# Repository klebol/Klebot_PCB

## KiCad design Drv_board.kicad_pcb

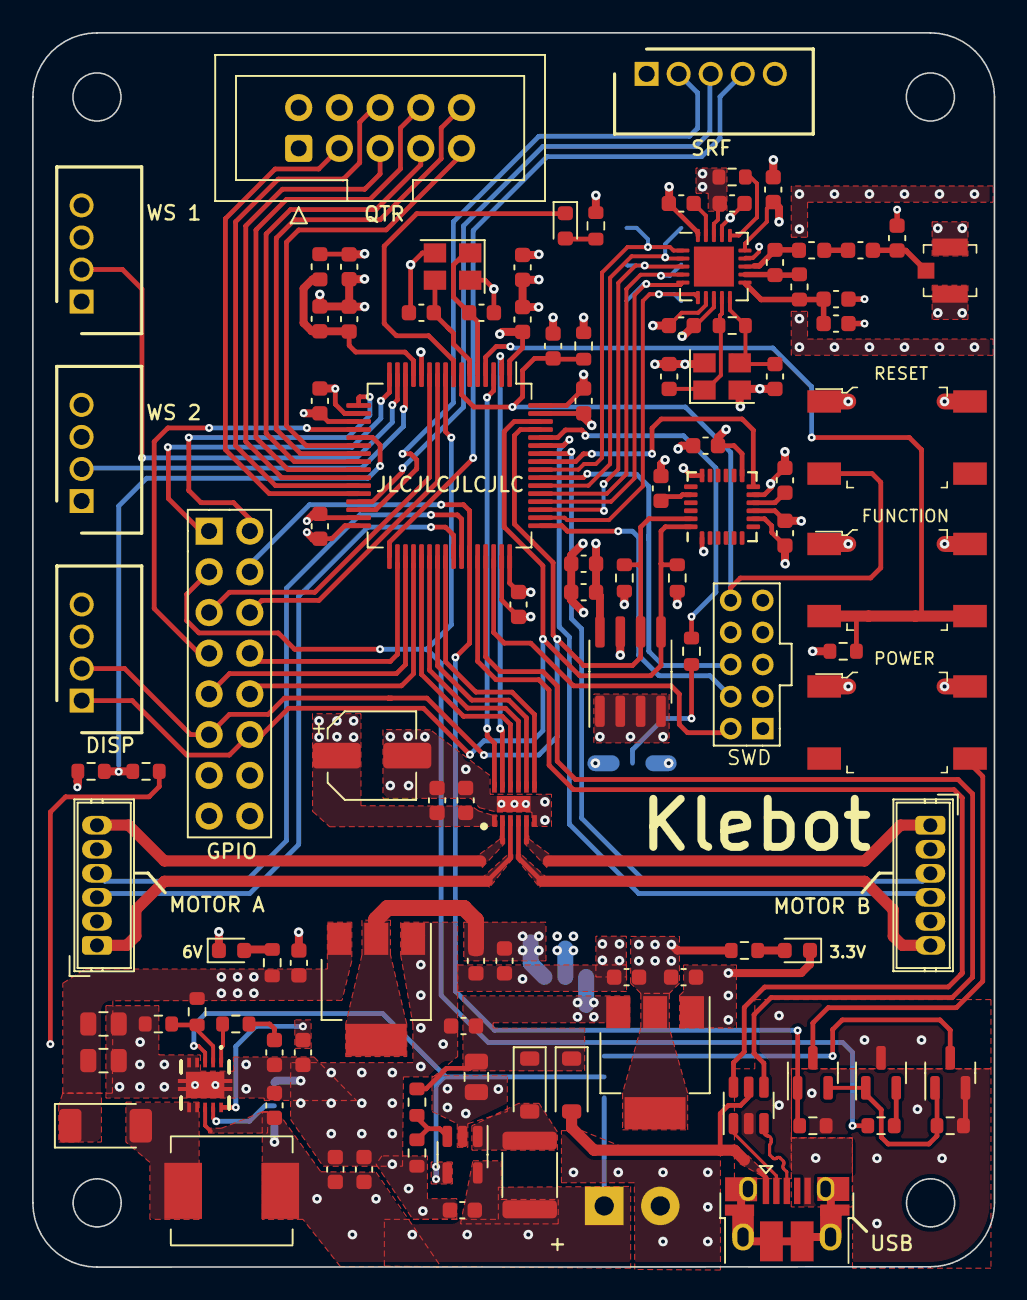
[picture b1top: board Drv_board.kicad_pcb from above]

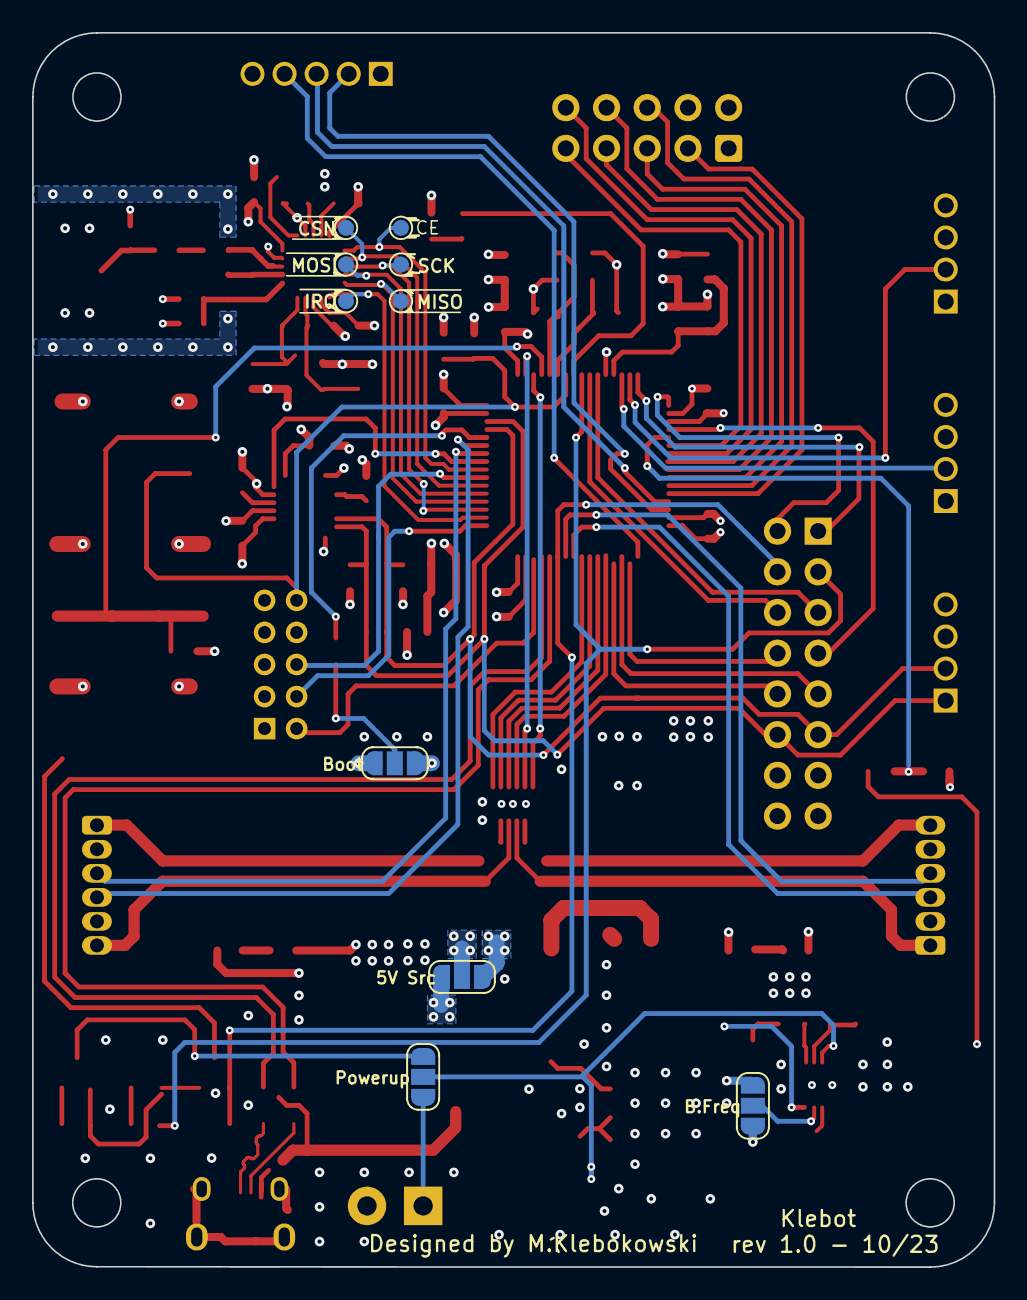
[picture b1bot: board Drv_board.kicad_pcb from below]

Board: 4 copper layers, 60.0 x 77.0 mm, 118 parts (10 on the bottom side), 96 nets.

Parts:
BT1: Battery; TerminalBlock_Phoenix_PT-1,5-2-3.5-H_1x02_P3.50mm_Horizontal
C1: 4u7; C_0603_1608Metric
C2, C3, C4, C5, C6, C10, C18, C20, C23, C25, C27, C30, C33, C34, C35, C42, C43, C45: 100n; C_0603_1608Metric
C7, C41: 10n; C_0603_1608Metric
C8, C9, C13: 1u; C_0603_1608Metric
C11, C12, C36, C37: 10p; C_0603_1608Metric
C14, C15, C19, C26, C29: 10u; C_0603_1608Metric
C16, C17: 22u; C_0805_2012Metric
C21: 4u7 6.3V; C_0603_1608Metric
C22: 22uF 6.3V; C_0805_2012Metric
C24: 2n7; C_0603_1608Metric
C28: 47u; CP_Elec_5x5.9
C31: 1p5; C_0603_1608Metric
C32: 1p; C_0603_1608Metric
C38, C46: 2n2; C_0603_1608Metric
C39: 4p7; C_0603_1608Metric
C40: 33n; C_0603_1608Metric
C44: 2u2; C_0603_1608Metric
D1: LED BLUE; LED_0603_1608Metric
D2: BAT54C; SOT-23
D3, D5: 40V 1A; D_SOD-123
D4: PMEG6030ETPX; D_SOD-128
D6: LED RED; LED_0603_1608Metric
D7: LED ORANGE; LED_0603_1608Metric
FB1: 120R; L_0603_1608Metric
IC1: TPS61087DRCR
IC2: DRV8836DSSR; SON50P200X300X80-13N-D
J1: USB_B_Micro; USB_Micro-B_Amphenol_10103594-0001LF_Horizontal
J2: WS_LED_1_CONN; SHDR4W55P0X200_1X4_1000X500X530P
J3: WS_LED_0_CONN; SHDR4W55P0X200_1X4_1000X500X530P
J4: QTR_CONN; IDC-Header_2x05_P2.54mm_Vertical
J5: SRF-05_CONN; SHDR5W55P0X200_1X5_1200X500X530P
J6: OLED_CONN; SHDR4W55P0X200_1X4_1000X500X530P
J7: SWD; PinHeader_2x05_P2.00mm_Vertical
J8: Motor A; Wuerth_WR-WTB_64800611622_1x06_P1.50mm_Vertical
J9: Motor B; Wuerth_WR-WTB_64800611622_1x06_P1.50mm_Vertical
J10: U.FL; Coax_Conn_U.FL
J11: BREAKOUT; PinHeader_2x08_P2.54mm_Vertical
JP1: 5V Source; SolderJumper-3_P1.3mm_Open_RoundedPad1.0x1.5mm
JP2: Powerup Mode; SolderJumper-3_P1.3mm_Open_RoundedPad1.0x1.5mm
JP3: Boost Converter Freqency; SolderJumper-3_P1.3mm_Open_RoundedPad1.0x1.5mm
L1: 4u7; L_Neosid_SM-PIC0602H
L2: 4.7uH 650mA; L_1812_4532Metric
L3: 3n9; L_0603_1608Metric
L4: 8n2; L_0603_1608Metric
L5: 2n7; L_0603_1608Metric
Q1: DMP2045U; SOT-23
Q2: BC847-QR; SOT-23
R1, R2, R4: 10k; R_0603_1608Metric
R3: ?; R_0603_1608Metric
R5, R6, R7, R8, R9: 100k; R_0603_1608Metric
R10: 69k8; R_0603_1608Metric
R11: 5k62; R_0603_1608Metric
R12: 330R; R_0603_1608Metric
R13: 1k; R_0603_1608Metric
R14: 18k; R_0603_1608Metric
R15: 16k; R_0603_1608Metric
R16: 1k87; R_0603_1608Metric
R17: 1M; R_0603_1608Metric
R18: 22k; R_0603_1608Metric
R19, R20: 2k2; R_0603_1608Metric
S1: RESET; Switch_Tactile_SMD_6x6mm
S2: USER_BUTTON; Switch_Tactile_SMD_6x6mm
S3: POWER UP; Switch_Tactile_SMD_6x6mm
SW1: SW_BOOT; SolderJumper-3_P1.3mm_Open_RoundedPad1.0x1.5mm
TP1: Test MOSI; TestPoint_Pad_D1.0mm
TP2: Test MISO; TestPoint_Pad_D1.0mm
TP3: Test SCK; TestPoint_Pad_D1.0mm
TP4: Test CSN; TestPoint_Pad_D1.0mm
TP5: Test CE; TestPoint_Pad_D1.0mm
TP6: Test IRQ; TestPoint_Pad_D1.0mm
U1: USBLC6-2SC6; SOT-23-6
U2: STM32F107RCTx; LQFP-64_10x10mm_P0.5mm
U3: LD1117S33; SOT-223-3_TabPin2
U4: MIC2288; TSOT-23-5
U5: LD1117S50; SOT-223-3_TabPin2
U6: nRF24L01P; QFN-20-1EP_4x4mm_P0.5mm_EP2.5x2.5mm
U7: M24C02-FMN; SOIC-8_3.9x4.9mm_P1.27mm
U8: MPU-6050; InvenSense_QFN-24_4x4mm_P0.5mm
Y1, Y2: 16 MHz; Crystal_SMD_3225-4Pin_3.2x2.5mm

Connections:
5V_Conv: C18.1, C22.1, D3.1 (K), D5.1 (K), JP1.3 (B), R11.1, U3.3 (VI)
5V_Stab: C26.1, C27.1, JP1.1 (A), U5.2 (VO)
+3.3V: C1.1, C2.1, C3.1, C4.1, C5.1, C6.1, C9.1, C19.1, C20.1, C33.1, C34.1, C35.1, C41.2, C42.2, C43.1, C44.1, FB1.2, J4.1, J6.3, J7.1, J8.5, J9.5, J11.14, R2.1, R3.2, R4.1, R12.1, R18.1, R19.1, R20.1, SW1.1 (A), U2.1 (VBAT), U2.19 (VDD), U2.32 (VDD), U2.48 (VDD), U2.64 (VDD), U3.2 (VO), U6.7 (VDD), U6.15 (VDD), U6.18 (VDD), U7.8 (VCC), U8.8 (VLOGIC), U8.13 (VDD)
+3.3VA: C7.1, C8.1, FB1.1, U2.13 (VDDA)
+5V: J2.3, J3.3, J5.1, J11.16, JP1.2 (C)
+6V: C16.1, C17.1, C25.1, C28.1, C29.1, C30.1, D4.1 (K), IC2.1 (VCC), R10.1, R13.1, U5.3 (VI)
+BATT: BT1.1 (+), C13.1, C14.1, C15.1, C21.1, IC1.8 (IN), JP2.1 (A), JP3.3 (B), L1.1, L2.1, Q1.2 (S), R5.1, R6.1, R7.2, U4.5 (VIN)
A1: IC2.2 (AOUT1), J8.6
A2: IC2.3 (AOUT2), J8.1
B1: IC2.4 (BOUT1), J9.6
B2: IC2.5 (BOUT2), J9.1
BATT_ADC_0: R7.1, R9.2, U2.21 (PA5)
BOOT0: R1.1, U2.60 (BOOT0)
DRV_AIN1/APHASE: IC2.10 (AIN1/APHASE), U2.37 (PC6)
DRV_AIN2/AENBL: IC2.9 (AIN2/AENBL), U2.38 (PC7)
DRV_BIN1/BPHASE: IC2.8 (BIN1_/_BPHASE), U2.39 (PC8)
DRV_BIN2/BENBL: IC2.7 (BIN2/BENBL), U2.40 (PC9)
DRV_MODE: IC2.11 (MODE), U2.2 (PC13)
DRV_NSLEEP: IC2.12 (NSLEEP), U2.3 (PC14)
EN: IC1.3 (EN), JP2.2 (C), U4.4 (EN)
ENC_A_1: J8.3, U2.41 (PA8)
ENC_A_2: J8.4, U2.42 (PA9)
ENC_B_1: J9.3, U2.58 (PB6)
ENC_B_2: J9.4, U2.59 (PB7)
EXT_PA4: J11.7, U2.20 (PA4)
EXT_PC2: J11.6, U2.10 (PC2)
EXT_PC3: J11.5, U2.11 (PC3)
EXT_SPI_MISO: J11.9, U2.35 (PB14)
EXT_SPI_MOSI: J11.10, U2.36 (PB15)
EXT_SPI_SCK: J11.8, U2.34 (PB13)
EXT_USART_RX: J11.2, U2.17 (PA3)
EXT_USART_TX: J11.1, U2.16 (PA2)
GND: BT1.2 (-), C1.2, C2.2, C3.2, C4.2, C5.2, C6.2, C7.2, C8.2, C9.2, C10.2, C11.2, C12.2, C13.2, C14.2, C15.2, C16.2, C17.2, C18.2, C19.2, C20.2, C21.2, C22.2, C23.2, C24.2, C25.2, C26.2, C27.2, C28.2, C29.2, C30.2, C32.2, C33.2, C34.2, C35.2, C36.2, C37.2, C38.1, C39.1, C40.2, C41.1, C42.1, C43.2, C44.2, C45.1, C46.1, D6.1 (K), D7.1 (K), IC1.4 (AGND_1), IC1.5 (PGND), IC1.11 (AGND_2), IC1.12 (AGND_3), IC1.13 (AGND_4), IC1.14 (AGND_5), IC1.15 (AGND_6), IC2.6 (GND_1), IC2.13 (GND_2), J1.5 (GND), J2.1, J2.4, J3.1, J3.4, J4.2, J5.5, J6.4, J7.3, J7.5, J7.9, J8.2, J9.2, J10.1, J11.13, J11.15, JP3.1 (A), Q2.3 (E), R9.1, R14.2, R16.2, S1.1, S1.2, S2.1, S2.2, S3.1, S3.2, SW1.3 (C), U1.2 (GND), U2.12 (VSSA), U2.18 (VSS), U2.31 (VSS), U2.47 (VSS), U2.63 (VSS), U3.1 (GND), U4.2 (GND), U5.1 (GND), U6.8 (VSS), U6.14 (VSS), U6.17 (VSS), U6.20 (VSS), U7.1 (E0), U7.2 (E1), U7.3 (E2), U7.4 (VSS), U7.7 (~WC), U8.1 (CLKIN), U8.9 (AD0), U8.11 (FSYNC), U8.18 (GND), Y1.2, Y1.4, Y2.2, Y2.4
I2C_SCL: J6.2, J11.11, R19.2, U2.61 (PB8), U7.6 (SCL), U8.23 (SCL)
I2C_SDA: J6.1, J11.12, R20.2, U2.62 (PB9), U7.5 (SDA), U8.24 (SDA)
KEEP_ALIVE: J11.3, R8.2, U2.9 (PC1)
LATCH_POWERUP: JP2.3 (B), Q1.3 (D)
MPU-6050_IRQ: U2.57 (PB5), U8.12 (INT)
NRF_ANT1: L4.2, L5.1, U6.12 (ANT1)
NRF_ANT2: L3.1, L4.1, U6.13 (ANT2)
NRF_CE: TP5.1, U2.56 (PB4), U6.1 (CE)
NRF_CSN: TP4.1, U2.54 (PD2), U6.2 (CSN)
NRF_IRQ: TP6.1, U2.50 (PA15), U6.6 (IRQ)
NRF_MISO: TP2.1, U2.52 (PC11), U6.5 (MISO)
NRF_MOSI: TP1.1, U2.53 (PC12), U6.4 (MOSI)
NRF_SCK: TP3.1, U2.51 (PC10), U6.3 (SCK)
NRF_VDD_PA: C38.2, C39.2, L5.2, U6.11 (VDD_PA)
NRF_XC1: C37.1, R17.2, U6.10 (XC1), Y2.3
NRF_XC2: C36.1, R17.1, U6.9 (XC2), Y2.1
NRST: C10.1, J7.10, R2.2, S1.3, U2.7 (NRST)
unnamed: C24.1, R15.2
unnamed: C31.1, L3.2
unnamed: C31.2, C32.1, J10.2
unnamed: D1.2 (A), R3.1
unnamed: D1.1 (K), U2.8 (PC0)
unnamed: D2.3, S3.4
unnamed: D4.2 (A), IC1.6 (SW_1), IC1.7 (SW_2), L1.2
unnamed: D5.2 (A), L2.2, U4.1 (SW)
unnamed: D6.2 (A), R12.2
unnamed: D7.2 (A), R13.2
unnamed: IC1.1 (COMP), R15.1
unnamed: IC1.2 (FB), R10.2, R14.1
unnamed: IC1.9 (FREQ), JP3.2 (C)
unnamed: C23.1, IC1.10 (SS)
unnamed: D2.2, Q1.1 (G), Q2.1 (C), R6.2
unnamed: Q2.2 (B), R8.1
unnamed: R1.2, SW1.2 (B)
unnamed: R4.2, S2.3, S2.4, U2.4 (PC15)
unnamed: C11.1, U2.5 (PD0), Y1.1
unnamed: C12.1, U2.6 (PD1), Y1.3
unnamed: R11.2, R16.1, U4.3 (FB)
unnamed: C40.1, U6.19 (DVDD)
unnamed: R18.2, U6.16 (IREF)
unnamed: C46.2, U8.20 (CPOUT)
unnamed: C45.2, U8.10 (REGOUT)
Power_Btn: D2.1, J11.4, R5.2, U2.43 (PA10)
QTR_0: J4.9, U2.22 (PA6)
QTR_1: J4.10, U2.23 (PA7)
QTR_2: J4.7, U2.24 (PC4)
QTR_3: J4.8, U2.25 (PC5)
QTR_4: J4.5, U2.26 (PB0)
QTR_5: J4.6, U2.27 (PB1)
QTR_CTRL: J4.3, U2.28 (PB2)
SRF-05_ECHO: J5.3, U2.29 (PB10)
SRF-05_IN: J5.4, U2.33 (PB12)
SRF-05_TRIG: J5.2, U2.30 (PB11)
SWCLK: J7.4, U2.49 (PA14)
SWDIO: J7.2, U2.46 (PA13)
SWO: J7.6, U2.55 (PB3)
USB_CONN_D+: J1.3 (D+), U1.3 (I/O2)
USB_CONN_D-: J1.2 (D-), U1.1 (I/O1)
USB_D+: U1.4 (I/O2), U2.45 (PA12)
USB_D-: U1.6 (I/O1), U2.44 (PA11)
V_USB: D3.2 (A), J1.1 (VBUS), U1.5 (VBUS)
WS_LED_0: J3.2, U2.15 (PA1)
WS_LED_1: J2.2, U2.14 (PA0)

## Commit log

2023-09-06 fixed footprint placement
2023-09-06 working on power
2023-09-08 Added power supply and motor schematics
2023-09-11 work progress
2023-09-12 most of the components added
2023-09-13 schematic completed
2023-09-18 done boost converter layout
2023-09-21 working
2023-09-29 working on pcb
2023-09-29 more layout added
2023-10-01 layout in progress
2023-10-02 more layout
2023-10-02 layout
2023-10-03 layout...
2023-10-05 layout finalising
2023-10-09 layout completed
2023-10-12 Completed PCB v1.0
